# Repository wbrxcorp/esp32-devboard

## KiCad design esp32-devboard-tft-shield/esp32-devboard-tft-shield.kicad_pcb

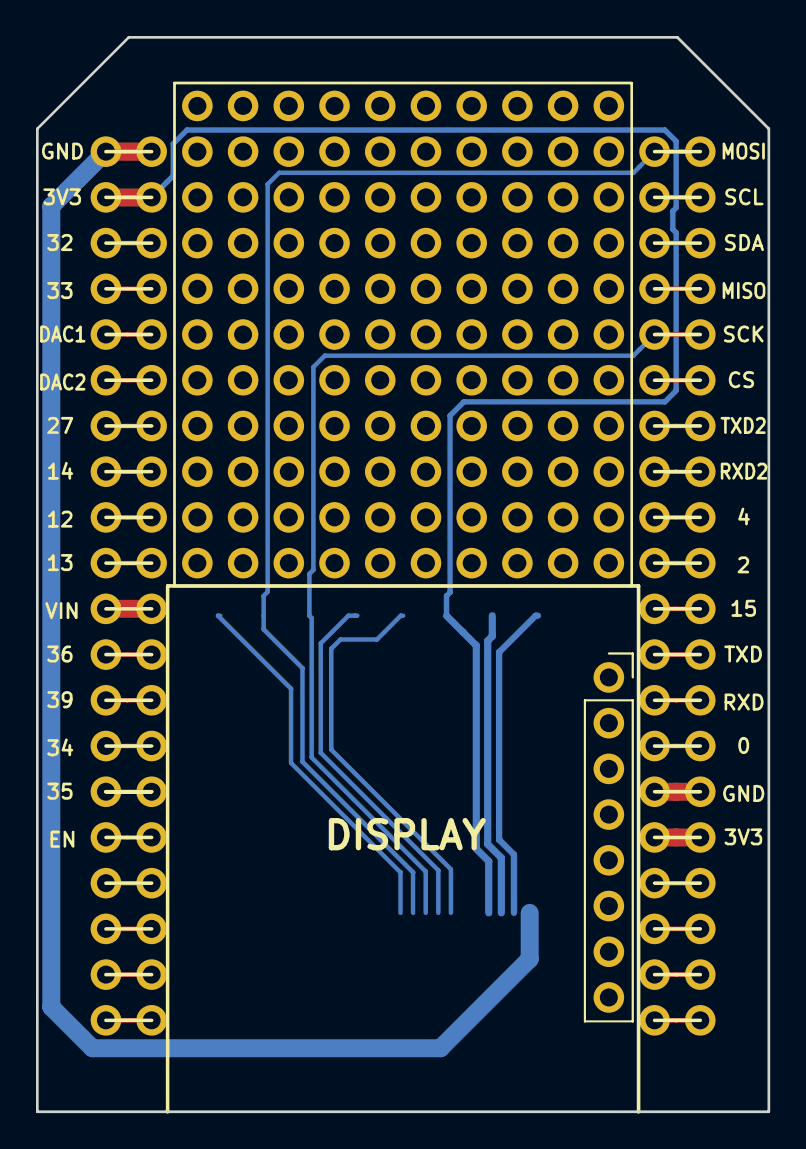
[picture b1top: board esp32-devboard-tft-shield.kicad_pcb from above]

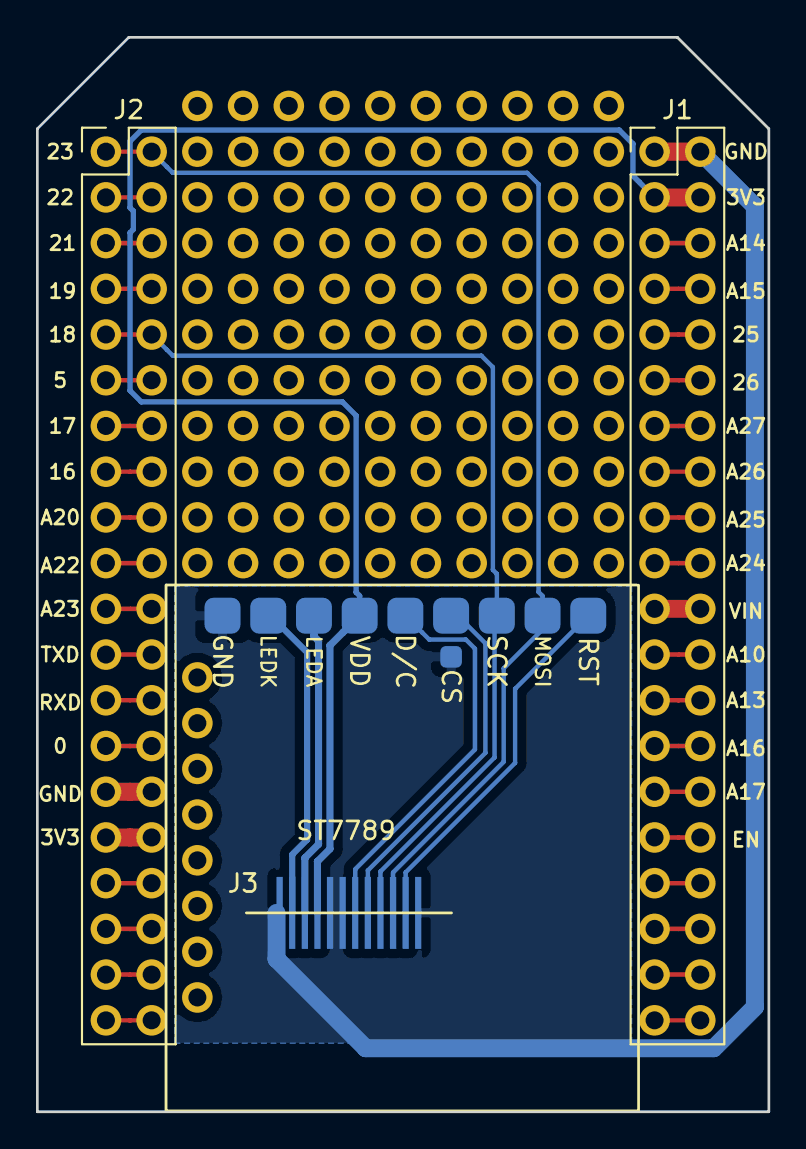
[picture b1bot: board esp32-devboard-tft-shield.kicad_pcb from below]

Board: 2 copper layers, 40.6 x 59.7 mm, 4 parts (3 on the bottom side), 40 nets.

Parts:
J1: Conn_02x20; PinHeader_2x20_P2.54mm_Vertical
J1#2: 11x10; Prototype_Area_2.54mm_11x10
J2: Conn_01x40; PinHeader_2x20_P2.54mm_Vertical
J3: Conn_01x12; TFT-12P

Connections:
/0: J2.27, J2.28
/2: J2.19, J2.20
/3V3: J1.3, J1.4, J3.4
/4: J2.17, J2.18
/12: J1.17, J1.18
/13: J1.19, J1.20
/14: J1.15, J1.16
/15: J2.21, J2.22
/27: J1.13, J1.14
/32: J1.5, J1.6
/33: J1.7, J1.8
/34: J1.27, J1.28
/35: J1.29, J1.30
/36: J1.23, J1.24
/39: J1.25, J1.26
/CS: J2.11, J2.12
/DAC1: J1.9, J1.10
/DAC2: J1.11, J1.12
/EN: J1.31, J1.32
/MISO: J2.7, J2.8
/MOSI: J2.1, J2.2, J3.10
/RXD: J2.25, J2.26
/RXD2: J2.15, J2.16
/SCK: J2.9, J2.10, J3.9
/SCL: J2.3, J2.4
/SDA: J2.5, J2.6
/TXD: J2.23, J2.24
/TXD2: J2.13, J2.14
/VIN: J1.21, J1.22
GND: J1.1, J1.2, J3.1, J3.5, J3.6, J3.12
unnamed: J1.33, J1.34
unnamed: J1.35, J1.36
unnamed: J1.37, J1.38
unnamed: J1.39, J1.40
unnamed: J2.29, J2.30
unnamed: J2.31, J2.32
unnamed: J2.33, J2.34
unnamed: J2.35, J2.36
unnamed: J2.37, J2.38
unnamed: J2.39, J2.40

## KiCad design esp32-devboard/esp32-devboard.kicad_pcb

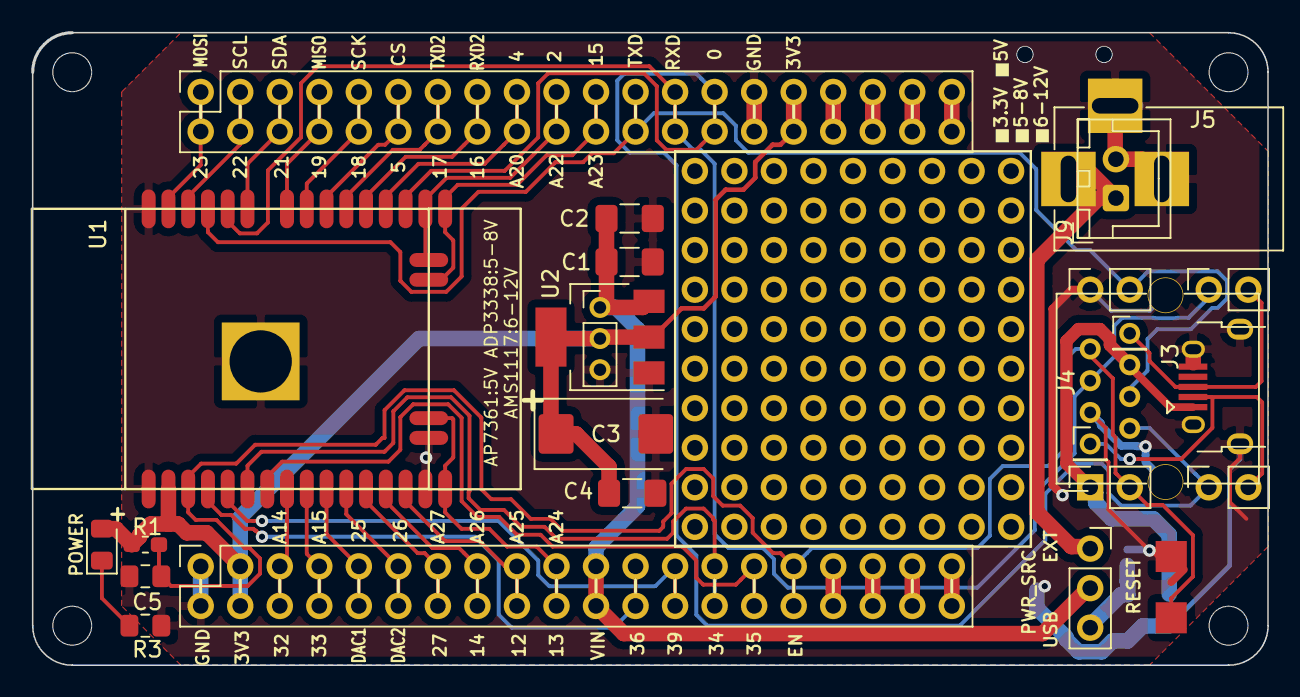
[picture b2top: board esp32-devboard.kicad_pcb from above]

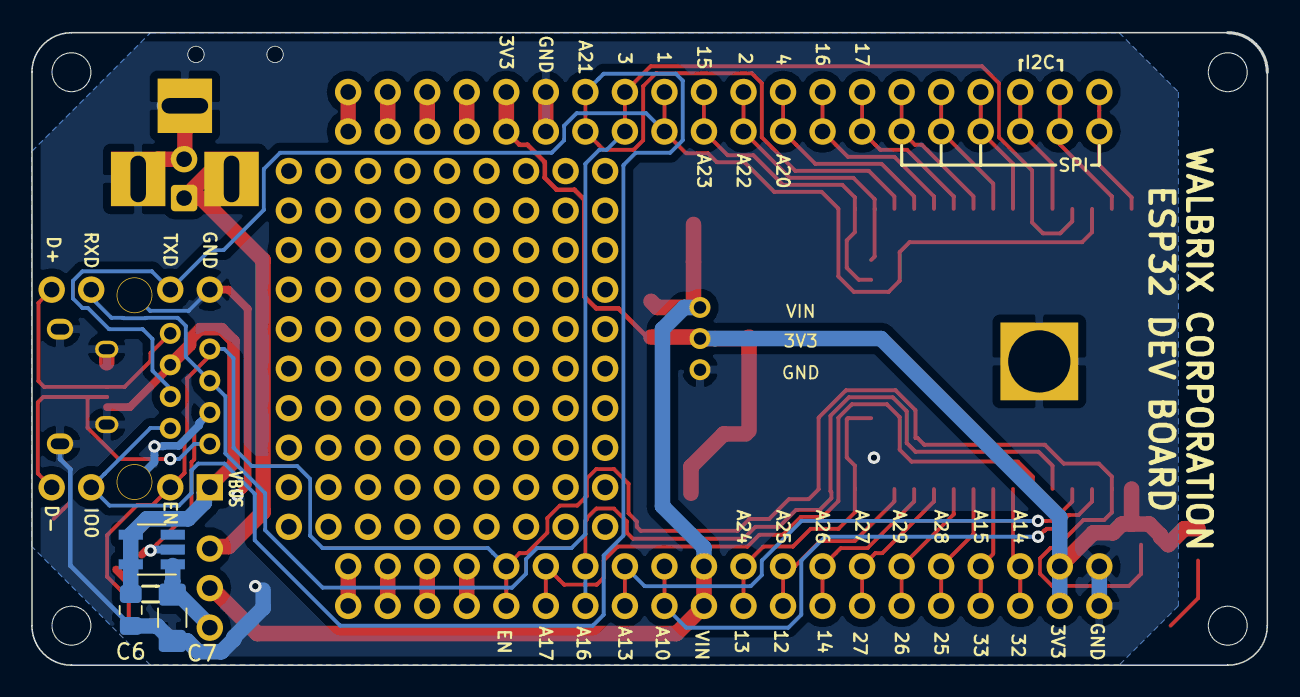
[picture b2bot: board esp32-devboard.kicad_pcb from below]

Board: 2 copper layers, 79.4 x 40.6 mm, 29 parts (3 on the bottom side), 44 nets.

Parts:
C1, C2, C4, C7: C; C_1206_3216Metric_Pad1.42x1.75mm_HandSolder
C3: C; CP_EIA-7343-15_Kemet-W_Pad2.25x2.55mm_HandSolder
C5: 1uF; C_0805_2012Metric_Pad1.15x1.40mm_HandSolder
C6: C; C_0805_2012Metric_Pad1.15x1.40mm_HandSolder
D1: LED; LED_0805_2012Metric_Pad1.15x1.40mm_HandSolder
J1, J2: Conn_01x40; PinSocket_2x20_P2.54mm_Vertical
J3: USB_B_Micro; USB_Micro-B_Horizontal
J4: RJ12
J5: Barrel_Jack_Switch; BARREL_JACK
J6, J7, J10, J11: Conn_01x02; PinSocket_1x02_P2.54mm_Vertical
J8: Conn_01x03; PinHeader_1x03_P2.00mm_Vertical
J9: Conn_01x02; JST_XH_B02B-XH-A_1x02_P2.50mm_Vertical
J12: TPS2065DBVR; SOT-23-5_HandSoldering
J13, J14: Conn_01x01; PinHeader_1x01_P2.00mm_Vertical
JX: 09x10; Prototype_Area_2.54mm_09x10
R1: 10K; R_0603_1608Metric_Pad1.05x0.95mm_HandSolder
R3: R; R_0805_2012Metric_Pad1.15x1.40mm_HandSolder
SW1: SW_Push; tactile_switch_smd_4x3mm_2p
SW2: SW_SPDT; PinSocket_1x03_P2.54mm_Vertical
U1: ESP32-WROOM-WROVER
U2: AMS1117-3.3; SOT-223-3_TabPin2

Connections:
/3V3: C3.1, C4.1, D1.2, J1.3, J1.4, J2.31, J2.32, J8.2, R1.1, U1.2, U2.2
/32: J1.5, J1.6, U1.8
/33: J1.7, J1.8, U1.9
/34: J1.27, J1.28, U1.6
/35: J1.29, J1.30, U1.7
/A0: J1.23, J1.24, U1.4
/A3: J1.25, J1.26, U1.5
/CS: J2.11, J2.12, U1.29
/D+: J3.3, J11.2, J13.1
/D-: J3.2, J10.2, J14.1
/DAC1: J1.9, J1.10, U1.10
/DAC2: J1.11, J1.12, U1.11
/EN: C5.1, J1.31, J1.32, J4.1, J6.2, R1.2, SW1.2, U1.3
/IO0: J2.27, J2.28, J4.6, J10.1, U1.25
/IO2: J2.19, J2.20, U1.24
/IO4: J2.17, J2.18, U1.26
/IO12: J1.17, J1.18, U1.14
/IO13: J1.19, J1.20, U1.16
/IO14: J1.15, J1.16, U1.13
/IO15: J2.21, J2.22, U1.23
/IO27: J1.13, J1.14, U1.12
/MISO: J2.7, J2.8, U1.31
/MOSI: J2.1, J2.2, U1.37
/RXD: J2.25, J2.26, J4.3, J11.1, U1.34
/RXD2: J2.15, J2.16, U1.27
/SCK: J2.9, J2.10, U1.30
/SCL: J2.3, J2.4, U1.36
/SDA: J2.5, J2.6, U1.33
/TXD: J2.23, J2.24, J4.4, J7.2, U1.35
/TXD2: J2.13, J2.14, U1.28
/USB_PWR: C7.1, J12.1, SW2.3
/VBUS: C6.1, J3.1, J4.2, J6.1, J12.4, J12.5
/VEXT: J5.1, J9.1, SW2.1
/VIN: C1.1, C2.1, J1.21, J1.22, J8.1, SW2.2, U2.3
GND: C1.2, C2.2, C3.2, C4.2, C5.2, C6.2, C7.2, J1.1, J1.2, J2.29, J2.30, J3.5, J3.6, J4.5, J5.2, J5.3, J7.1, J8.3, J9.2, J12.2, R3.2, SW1.1, U1.1, U1.15, U1.38, U1.39, U2.1
unnamed: D1.1, R3.1
unnamed: J1.33, J1.34
unnamed: J1.35, J1.36
unnamed: J1.37, J1.38
unnamed: J1.39, J1.40
unnamed: J2.33, J2.34
unnamed: J2.35, J2.36
unnamed: J2.37, J2.38
unnamed: J2.39, J2.40

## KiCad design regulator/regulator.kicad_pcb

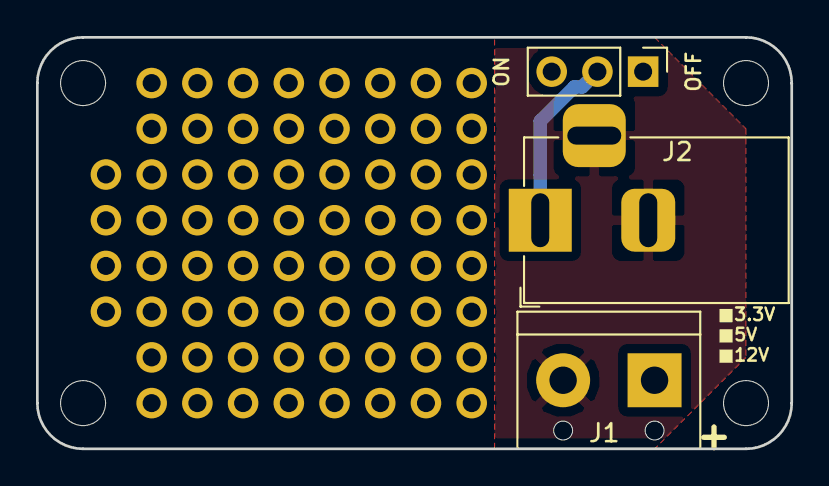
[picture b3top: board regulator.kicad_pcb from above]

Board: 2 copper layers, 41.9 x 22.9 mm, 5 parts (0 on the bottom side), 2 nets.

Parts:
J1: 0x04; Prototype_Area_2.54mm_01x04
J1#2: Conn_01x02; TerminalBlock_bornier-2_P5.08mm
J2: Barrel_Jack_Switch; BarrelJack_Horizontal
J10: 09x10; Prototype_Area_2.54mm_08x08
SW1: SW_SPDT; PinHeader_1x03_P2.54mm_Vertical

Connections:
GND: J1#2.2, J2.2, J2.3
unnamed: J2.1, SW1.2

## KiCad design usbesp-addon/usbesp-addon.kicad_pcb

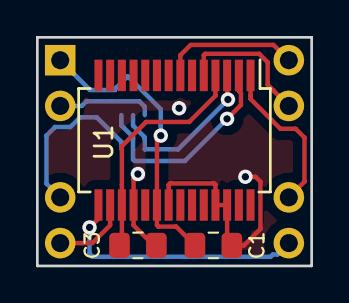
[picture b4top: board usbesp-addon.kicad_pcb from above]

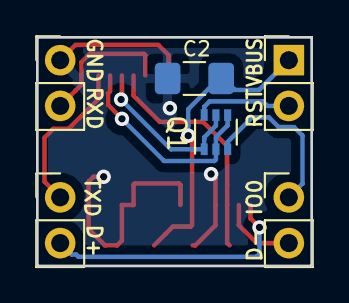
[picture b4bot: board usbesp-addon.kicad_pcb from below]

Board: 2 copper layers, 15.2 x 12.7 mm, 9 parts (6 on the bottom side), 11 nets.

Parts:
C1, C3: 0.1uF; C_0805_2012Metric_Pad1.15x1.40mm_HandSolder
C2: 10uF; C_1206_3216Metric_Pad1.42x1.75mm_HandSolder
J1, J2, J3, J4: Conn_01x02; PinHeader_1x02_P2.54mm_Vertical
Q1: BC847BS; SOT-363_SC-70-6
U1: FT232RL; SSOP-28_5.3x10.2mm_P0.65mm

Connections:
/3v3: C3.1, U1.4, U1.17
/DTR: Q1.2, Q1.4, U1.2
/IO0: J1.1, Q1.3
/RESET: J2.2, Q1.6
/RTS: Q1.1, Q1.5, U1.3
/RXD: J3.2, U1.5
/TXD: J4.1, U1.1
/USBDM: J1.2, U1.16
/USBDP: J4.2, U1.15
/VBUS: C1.1, C2.1, J2.1, U1.20
GND: C1.2, C2.2, C3.2, J3.1, U1.7, U1.18, U1.21, U1.25, U1.26

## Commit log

2019-02-11 begin with 3 boards
2019-02-22 usbesp-rj12 moved from other project
2019-03-03 PCB update
2019-03-03 Quarter shield added
2019-03-04 regulator board added
2019-03-05 change pinouts
2019-03-05 prototype area enlarged
2019-03-05 follow pinout changes
2019-03-06 add 3v3 pin for external device
2019-03-06 regulator update
2019-03-06 add/enlarge holes
2019-03-09 add ST7789(no cs pin) driver (incomplete)
2019-03-09 remove delay
2019-03-14 ESP32-WROVER support
2019-03-20 TFT shield added
2019-03-20 ammeter added
2019-03-20 fix socket location
2019-03-22 tft shield update
2019-03-22 use native_memory module
